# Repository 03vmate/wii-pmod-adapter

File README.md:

# wii-pmod-adapter
A generic PMOD breakout board, used for interfacing with a Wii's AVE-RVL in my case

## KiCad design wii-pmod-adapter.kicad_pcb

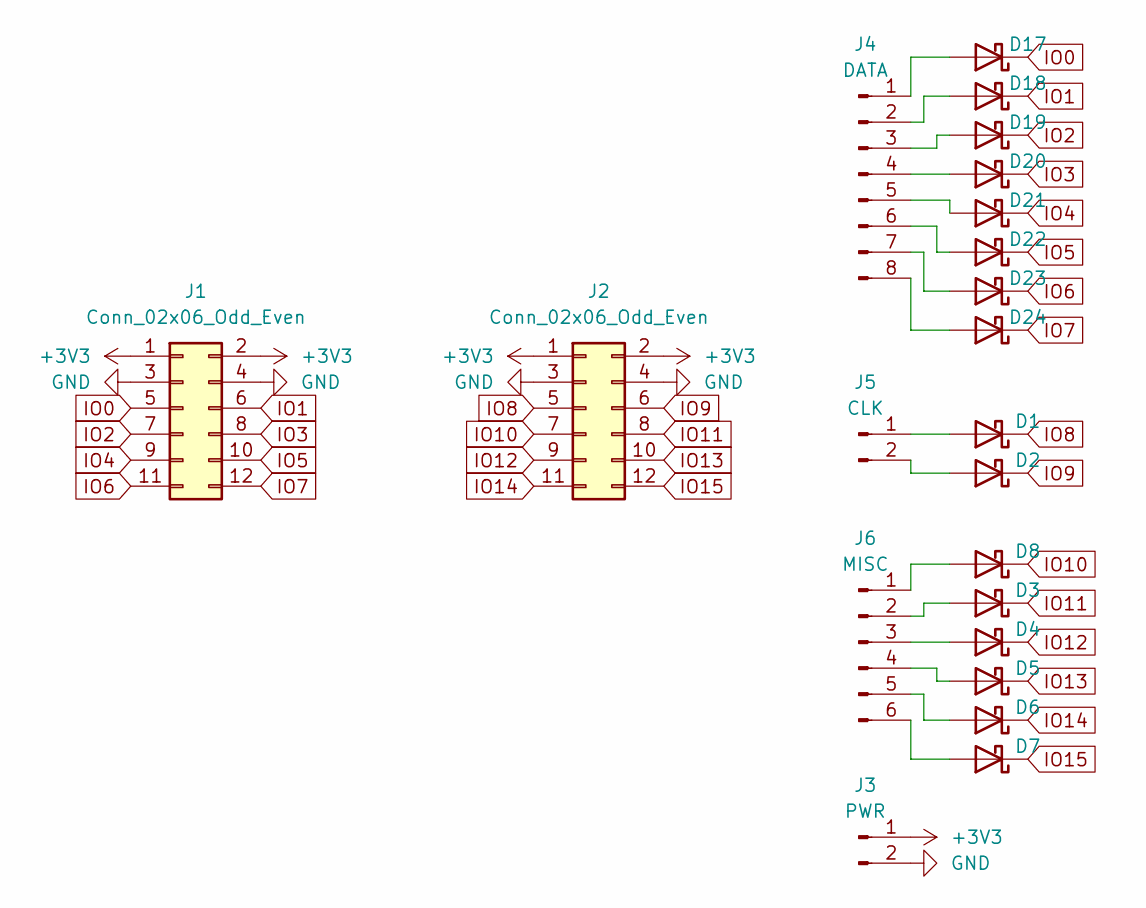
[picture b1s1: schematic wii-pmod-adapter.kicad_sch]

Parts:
D1, D2, D3, D4, D5, D6, D7, D8, D17, D18, D19, D20, D21, D22, D23, D24: D_Schottky; D_SOD-123
J1, J2: Conn_02x06_Odd_Even; PinHeader_2x06_P2.54mm_Vertical
J3: PWR; JST_PH_B2B-PH-K_1x02_P2.00mm_Vertical
J4: DATA; JST_PH_B8B-PH-K_1x08_P2.00mm_Vertical
J5: CLK; JST_PH_B2B-PH-K_1x02_P2.00mm_Vertical
J6: MISC; JST_PH_B6B-PH-K_1x06_P2.00mm_Vertical

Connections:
+3V3: J1.1, J1.2, J2.1, J2.2, J3.1
GND: J1.3, J1.4, J2.3, J2.4, J3.2
IO0: D17.1 (K), J1.5
IO1: D18.1 (K), J1.6
IO2: D19.1 (K), J1.7
IO3: D20.1 (K), J1.8
IO4: D21.1 (K), J1.9
IO5: D22.1 (K), J1.10
IO6: D23.1 (K), J1.11
IO7: D24.1 (K), J1.12
IO8: D1.1 (K), J2.5
IO9: D2.1 (K), J2.6
IO10: D8.1 (K), J2.7
IO11: D3.1 (K), J2.8
IO12: D4.1 (K), J2.9
IO13: D5.1 (K), J2.10
IO14: D6.1 (K), J2.11
IO15: D7.1 (K), J2.12
unnamed: D1.2 (A), J5.1
unnamed: D2.2 (A), J5.2
unnamed: D3.2 (A), J6.2
unnamed: D4.2 (A), J6.3
unnamed: D5.2 (A), J6.4
unnamed: D6.2 (A), J6.5
unnamed: D7.2 (A), J6.6
unnamed: D8.2 (A), J6.1
unnamed: D17.2 (A), J4.1
unnamed: D18.2 (A), J4.2
unnamed: D19.2 (A), J4.3
unnamed: D20.2 (A), J4.4
unnamed: D21.2 (A), J4.5
unnamed: D22.2 (A), J4.6
unnamed: D23.2 (A), J4.7
unnamed: D24.2 (A), J4.8

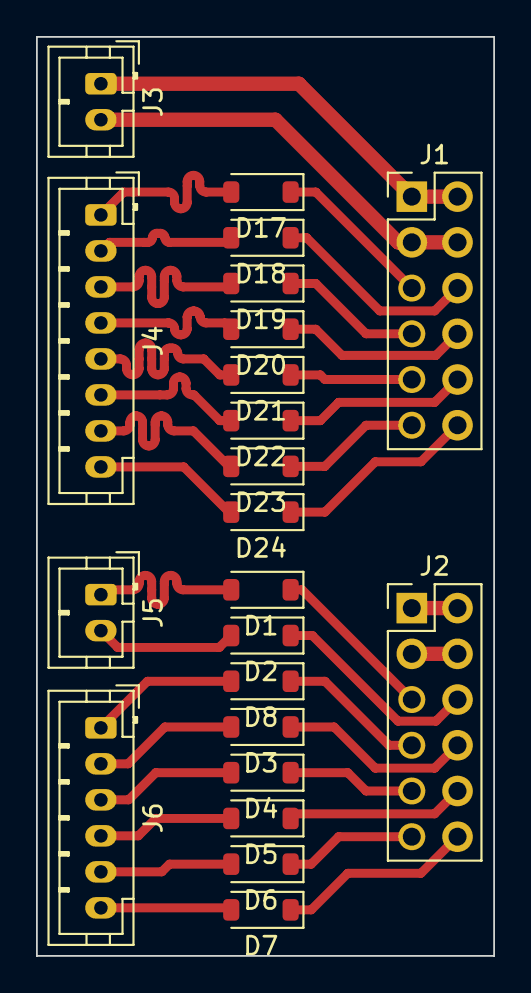
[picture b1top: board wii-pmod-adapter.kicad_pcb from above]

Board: 2 copper layers, 25.4 x 51.1 mm, 22 parts (0 on the bottom side), 34 nets.

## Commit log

2024-01-09 Schematic
2024-01-09 Early layout
2024-01-11 Remove unnecessary files
2024-01-11 Add gitignore
2024-01-11 Routed PMOD1
2024-01-11 Routing done
